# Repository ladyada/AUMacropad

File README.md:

# AUMacropad
Contains design files for AU Macropad which is a modded version of the Adafruit Macropad

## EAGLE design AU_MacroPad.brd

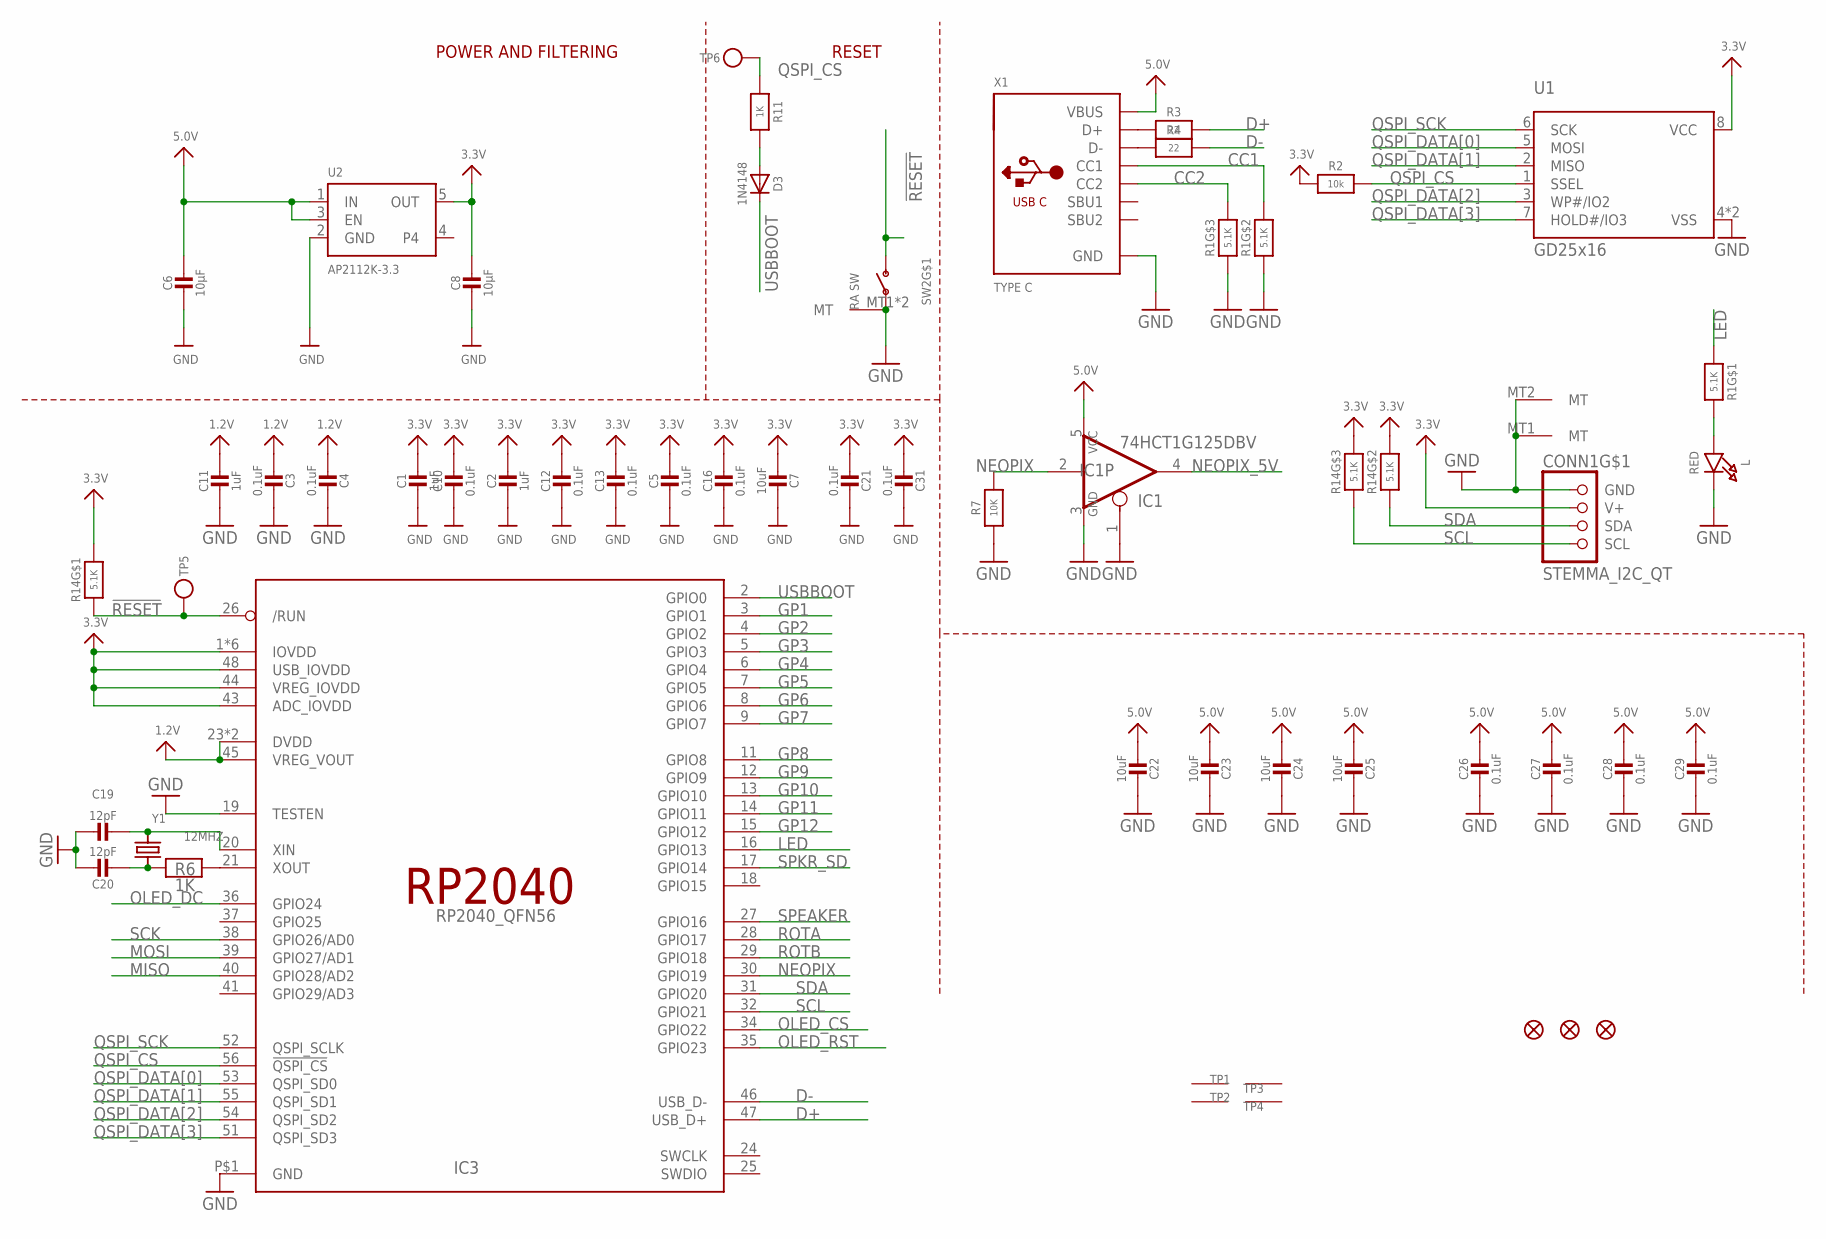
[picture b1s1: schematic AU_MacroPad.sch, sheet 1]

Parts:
C1, C2, C11: 1uF; 0603-NO
C3, C4, C5, C10, C12, C13, C16, C21, C26, C27, C28, C29, C31: 0.1uF; 0603-NO
C6, C8: 10µF; 0805-NO
C7, C22, C23, C24, C25: 10uF; 0805-NO
C19, C20: 12pF; 0603-NO
CONN1: STEMMA_I2C_QT; JST_SH4
D3: 1N4148; SOD-323
IC1: 74HCT1G125DBV; SOT23-5
IC3: RP2040_QFN56; QFN56_7MM_REDUCEDEPAD
L: RED; CHIPLED_0603_NOOUTLINE
R1, R14: 5.1K; RESPACK_4X0603
R2: 10k; 0603-NO
R3, R4: 22; 0603-NO
R6, R11: 1K; 0603-NO
R7: 10K; 0603-NO
SW2: RA SW; SPST_TACTILE_RA
TP1, TP2, TP3, TP4: SEWTAP_SMTNUTM3; SMT_NUT_3MM
TP5, TP6: TESTPOINTROUND1.5MMNO; TESTPOINT_ROUND_1.5MM_NO
U1: GD25x16; USON8_4X4
U2: AP2112K-3.3; SOT23-5
U$34, U$35, U$80: FIDUCIAL_1MM
X1: TYPE C; USB_C_CUSB31-CFM2AX-01-X
Y1: 12MHZ; CRYSTAL_2.5X2

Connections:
1.2V: C3.2, C4.2, C11.1, IC3.23 (DVDD), IC3.45 (VREG_VOUT), IC3.50 (DVDD)
3.3V: C1.1, C2.1, C5.1, C7.2, C8.1, C10.1, C12.1, C13.1, C16.1, C21.2, C31.2, CONN1.2 (V+), IC3.1 (IOVDD), IC3.10 (IOVDD), IC3.22 (IOVDD), IC3.33 (IOVDD), IC3.42 (IOVDD), IC3.43 (ADC_IOVDD), IC3.44 (VREG_IOVDD), IC3.48 (USB_IOVDD), IC3.49 (IOVDD), R2.1, R14.6 (2), R14.7 (2), R14.8 (2), U1.8 (VCC), U2.5 (OUT); also elsewhere on the board
!RESET: IC3.26 (/RUN), R14.1, SW2.2 (S), TP5.P$1
CC1: R1.7 (2), X1.A5 (CC1)
CC2: R1.6 (2), X1.B5 (CC2)
D+: IC3.47 (USB_D+), R3.2
D-: IC3.46 (USB_D-), R4.2
GP1: IC3.3 (GPIO1); also elsewhere on the board
GP2: IC3.4 (GPIO2); also elsewhere on the board
GP3: IC3.5 (GPIO3); also elsewhere on the board
GP4: IC3.6 (GPIO4); also elsewhere on the board
GP5: IC3.7 (GPIO5); also elsewhere on the board
GP6: IC3.8 (GPIO6); also elsewhere on the board
GP7: IC3.9 (GPIO7); also elsewhere on the board
GP8: IC3.11 (GPIO8); also elsewhere on the board
GP9: IC3.12 (GPIO9); also elsewhere on the board
GP10: IC3.13 (GPIO10); also elsewhere on the board
GP11: IC3.14 (GPIO11); also elsewhere on the board
GP12: IC3.15 (GPIO12); also elsewhere on the board
LED: IC3.16 (GPIO13), R1.1
MISO: IC3.40 (GPIO28/AD2)
MOSI: IC3.39 (GPIO27/AD1); also elsewhere on the board
unnamed: R3.1, X1.A6 (D+), X1.B6 (D+)
unnamed: L.A, R1.8 (2)
unnamed: R4.1, X1.A7 (D-), X1.B7 (D-)
unnamed: D3.A, R11.2
unnamed: C19.2, IC3.20 (XIN), Y1.3 (2)
unnamed: C20.2, R6.1, Y1.1
unnamed: IC3.21 (XOUT), R6.2
NEOPIX: IC1.2 (I), IC3.30 (GPIO19), R7.2
NEOPIX_5V: IC1.4 (O); also elsewhere on the board
OLED_CS: IC3.34 (GPIO22); also elsewhere on the board
OLED_DC: IC3.36 (GPIO24); also elsewhere on the board
OLED_RST: IC3.35 (GPIO23); also elsewhere on the board
QSPI_CS: IC3.56 (!QSPI_CS), R2.2, R11.1, TP6.P$1, U1.1 (SSEL)
QSPI_DATA[0]: IC3.53 (QSPI_SD0), U1.5 (MOSI)
QSPI_DATA[1]: IC3.55 (QSPI_SD1), U1.2 (MISO)
QSPI_DATA[2]: IC3.54 (QSPI_SD2), U1.3 (WP#/IO2)
QSPI_DATA[3]: IC3.51 (QSPI_SD3), U1.7 (HOLD#/IO3)
QSPI_SCK: IC3.52 (QSPI_SCLK), U1.6 (SCK)
ROTA: IC3.28 (GPIO17); also elsewhere on the board
ROTB: IC3.29 (GPIO18); also elsewhere on the board
SCK: IC3.38 (GPIO26/AD0); also elsewhere on the board
SCL: CONN1.4 (SCL), IC3.32 (GPIO21), R14.3 (1)
SDA: CONN1.3 (SDA), IC3.31 (GPIO20), R14.2 (1)
SPEAKER: IC3.27 (GPIO16); also elsewhere on the board
SPKR_SD: IC3.17 (GPIO14); also elsewhere on the board

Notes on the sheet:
POWER AND FILTERING
RESET

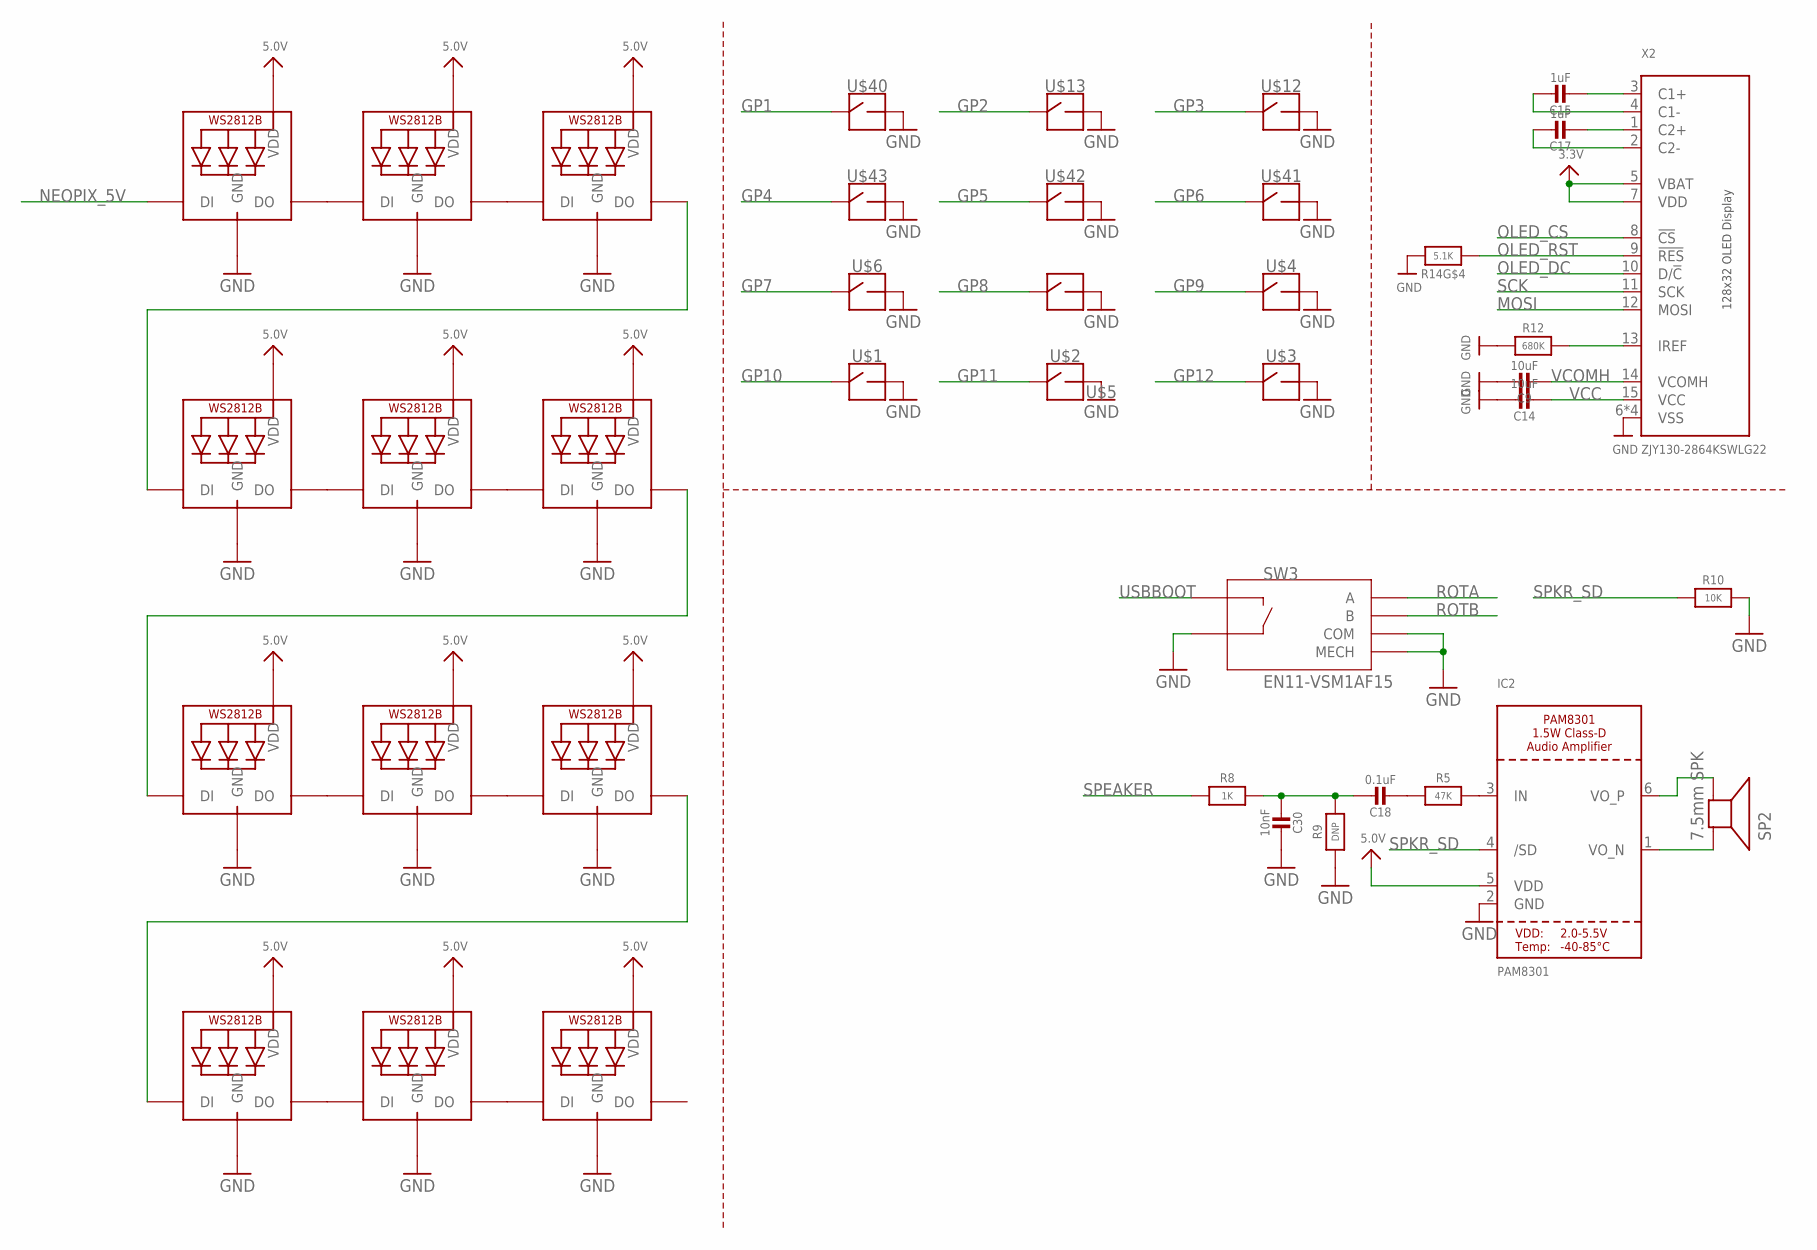
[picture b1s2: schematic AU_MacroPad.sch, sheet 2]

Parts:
C9, C14: 10uF; 0805-NO
C15, C17: 1uF; 0603-NO
C18: 0.1uF; 0603-NO
C30: 10nF; 0603-NO
IC2: PAM8301; SOT23-6
LED1, LED2, LED3, LED4, LED5, LED6, LED7, LED8, LED9, LED10, LED11, LED12: WS2812B_SK6812E; NEO3535_REVERSE
R5: 47K; 0603-NO
R8: 1K; 0603-NO
R9: DNP; 0603-NO
R10: 10K; 0603-NO
R12: 680K; 0603-NO
R14: 5.1K; RESPACK_4X0603
SP2: 7.5mm SPK; BUZZER_SMT_7.5MM
SW3: EN11-VSM1AF15
U$1, U$2, U$3, U$4, U$5, U$6, U$12, U$13, U$40, U$41, U$42, U$43: SOCKET; KAILH_SOCKET
X2: ZJY130-2864KSWLG22

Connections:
3.3V: X2.5 (VBAT), X2.7 (VDD); also elsewhere on the board
GP1: U$40.1; also elsewhere on the board
GP2: U$13.1; also elsewhere on the board
GP3: U$12.1; also elsewhere on the board
GP4: U$43.1; also elsewhere on the board
GP5: U$42.1; also elsewhere on the board
GP6: U$41.1; also elsewhere on the board
GP7: U$6.1; also elsewhere on the board
GP8: U$5.1; also elsewhere on the board
GP9: U$4.1; also elsewhere on the board
GP10: U$1.1; also elsewhere on the board
GP11: U$2.1; also elsewhere on the board
GP12: U$3.1; also elsewhere on the board
MOSI: X2.12 (MOSI); also elsewhere on the board
unnamed: LED1.2-DOUT (DO), LED2.4-DIN (DI)
unnamed: LED2.2-DOUT (DO), LED3.4-DIN (DI)
unnamed: LED4.2-DOUT (DO), LED5.4-DIN (DI)
unnamed: LED5.2-DOUT (DO), LED6.4-DIN (DI)
unnamed: LED7.2-DOUT (DO), LED8.4-DIN (DI)
unnamed: LED8.2-DOUT (DO), LED9.4-DIN (DI)
unnamed: LED10.2-DOUT (DO), LED11.4-DIN (DI)
unnamed: LED11.2-DOUT (DO), LED12.4-DIN (DI)
unnamed: LED3.2-DOUT (DO), LED4.4-DIN (DI)
unnamed: LED6.2-DOUT (DO), LED7.4-DIN (DI)
unnamed: LED9.2-DOUT (DO), LED10.4-DIN (DI)
unnamed: R12.2, X2.13 (IREF)
unnamed: C17.1, X2.2 (C2-)
unnamed: C17.2, X2.1 (C2+)
unnamed: C15.1, X2.4 (C1-)
unnamed: C15.2, X2.3 (C1+)
NEOPIX_5V: LED1.4-DIN (DI); also elsewhere on the board
unnamed: IC2.1 (VO_N), SP2.+
unnamed: IC2.3 (IN), R5.2
unnamed: IC2.4 (/SD), R10.1
unnamed: IC2.6 (VO_P), SP2.-
OLED_CS: X2.8 (!CS); also elsewhere on the board
OLED_DC: X2.10 (D/!C); also elsewhere on the board
OLED_RST: R14.4 (1), X2.9 (!RES); also elsewhere on the board
ROTA: SW3.A; also elsewhere on the board
ROTB: SW3.B; also elsewhere on the board
SCK: X2.11 (SCK); also elsewhere on the board
VCC: C14.2, X2.15 (VCC)
VCOMH: C9.2, X2.14 (VCOMH)

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
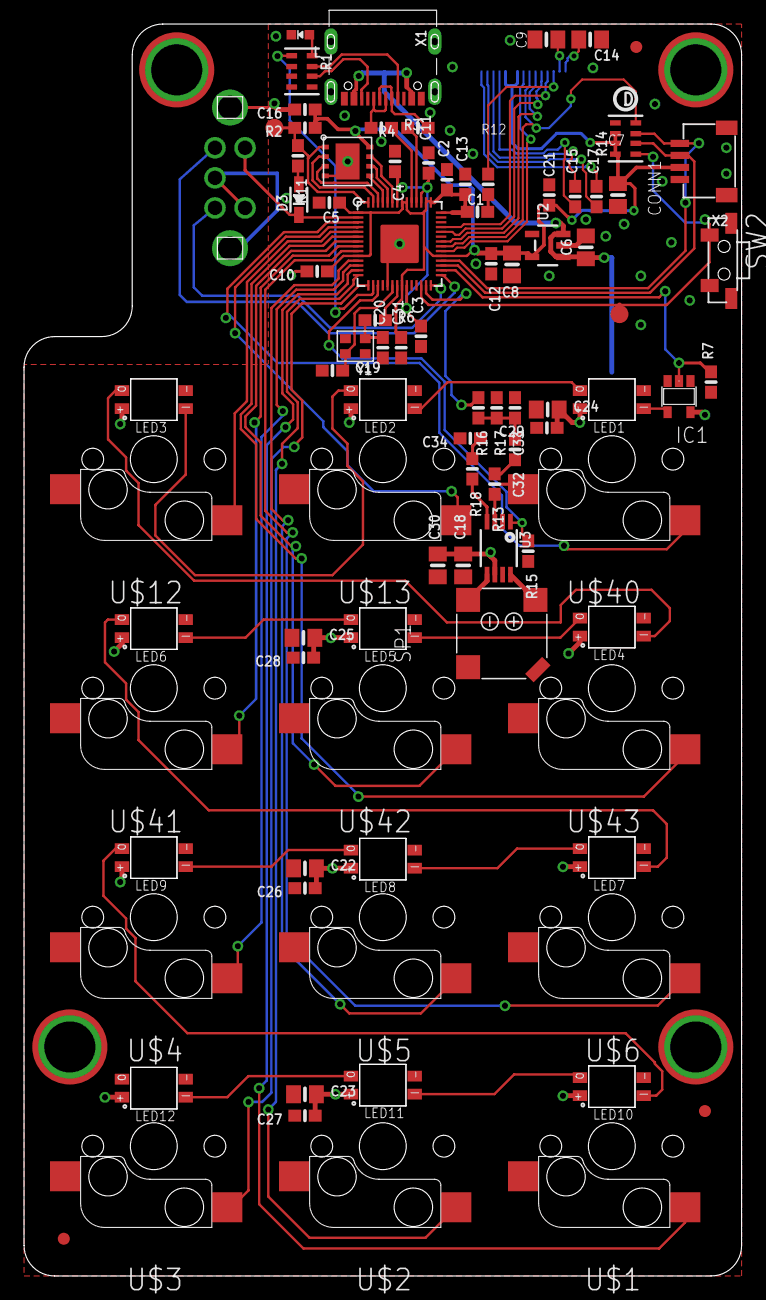
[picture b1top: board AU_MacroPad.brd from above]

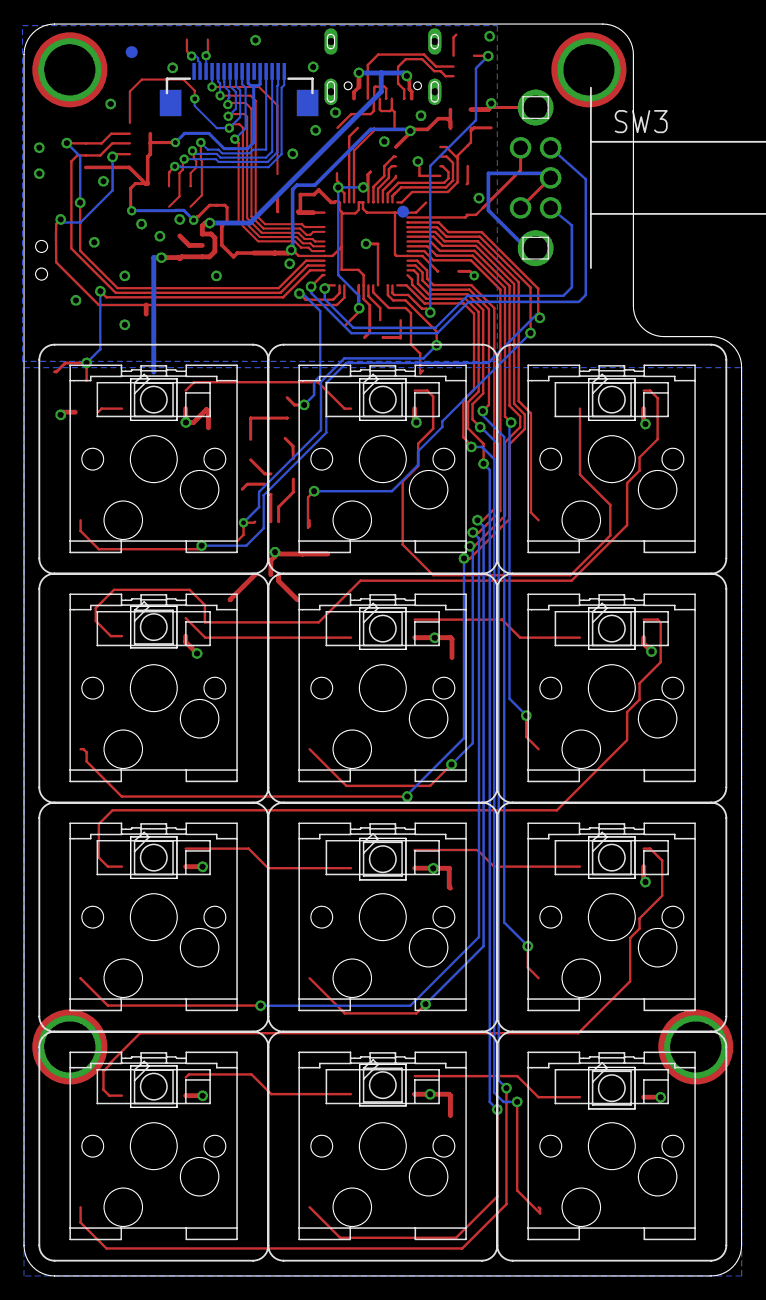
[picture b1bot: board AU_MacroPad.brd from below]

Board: 2 copper layers, 59.6 x 104.0 mm, 98 parts (27 on the bottom side), 74 nets.

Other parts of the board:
C32, C34: 0.1uF; 0603-NO
C33: 10nF; 0603-NO
R13, R18: 47K; 0603-NO
R15: 10K; 0603-NO
R16: 1K; 0603-NO
R17: DNP; 0603-NO
SP1: 7.5mm SPK; BUZZER_SMT_7.5MM
U3: PAM8302; MSOP8_0.65MM
U$79, U$83: FIDUCIAL_1MM
U$81: PCBFEAT-REV-040

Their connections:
IN+: R13.2, U3.3
IN-: R18.2, U3.4
unnamed: C32.2, R13.1
unnamed: C32.1, C33.2, R16.2, R17.2
unnamed: C34.1, R18.1
unnamed: SP1.-, U3.5
unnamed: SP1.+, U3.8
SPEAKER: R16.1; also elsewhere on the board
SPKR_SD: R15.1, U3.1; also elsewhere on the board

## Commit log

2023-06-06 swap gnd and usbboot to match original macropad
2023-06-06 add bottom fiducials, clean up silk due to other side OLED
2023-08-16 Connector rotated 180 degrees and traces re-routed
2023-08-21 Add files via upload
    Built from Limor's files. Rotated connector 180 degrees and re-routed.
2023-08-21 rotated connector
2023-08-21 updated library
2023-09-25 panelized
2024-05-15 added encoder!

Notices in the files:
parts and their libraries:
microbuilder: This work is placed in the public domain, and may be freely used for commercial and non-commercial work with the following conditions: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
